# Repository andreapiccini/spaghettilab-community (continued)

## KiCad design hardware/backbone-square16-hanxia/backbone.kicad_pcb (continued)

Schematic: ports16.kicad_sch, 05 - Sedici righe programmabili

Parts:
C238, C239, C241, C242: 100nF; C_0603_1608Metric
J18, J19, J21, J22, J23, J24, J30, J31: HX PM2.54-1x8P TP-YQ; Hanxia_C42380985_1x08_Compact_Study; MPN HX PM2.54-1x8P TP-YQ; LCSC Part C42380985
Q30, Q31, Q32, Q33, Q34, Q35, Q36, Q37, Q44, Q45, Q46, Q47, Q48, Q49, Q50, Q51: AO3401A; SOT-23; MPN AO3401A; LCSC Part C15127
Q100, Q101, Q102, Q103, Q104, Q105, Q106, Q107, Q108, Q109, Q110, Q111, Q112, Q113, Q114, Q115: AO3400A; SOT-23; MPN AO3400A; LCSC Part C20917
RN1, RN2, RN3, RN4, RN5, RN6, RN7, RN8, RN9, RN10, RN11, RN12: 100k; YC164_4x0603_100k
U1: ESP32-S3-WROOM-1-N8R2; ESP32-S3-WROOM-1_FlexyPin_N8R2_TwoSideCourtyard; MPN ESP32-S3-WROOM-1-N8R2
U50, U51, U53, U54: 74CBTLV3125PW,118; TSSOP-14_L5.0-W4.4-P0.65-LS6.4-BL; MPN 74CBTLV3125PW,118; LCSC Part C456149

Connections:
3V3: C238.1, C239.1, C241.1, C242.1, RN9.1, RN9.2, RN9.3, RN9.4, RN10.1, RN10.2, RN10.3, RN10.4, RN11.1, RN11.2, RN11.3, RN11.4, RN12.1, RN12.2, RN12.3, RN12.4, U50.14 (VCC), U51.14 (VCC), U53.14 (VCC), U54.14 (VCC); also elsewhere on the board
3V3_ROWS: Q30.2 (S), Q31.2 (S), Q32.2 (S), Q33.2 (S), Q34.2 (S), Q35.2 (S), Q36.2 (S), Q37.2 (S), Q44.2 (S), Q45.2 (S), Q46.2 (S), Q47.2 (S), Q48.2 (S), Q49.2 (S), Q50.2 (S), Q51.2 (S), RN1.1, RN1.2, RN1.3, RN1.4, RN2.1, RN2.2, RN2.3, RN2.4, RN3.1, RN3.2, RN3.3, RN3.4, RN4.1, RN4.2, RN4.3, RN4.4; also elsewhere on the board
GND: C238.2, C239.2, C241.2, C242.2, Q100.2 (S), Q101.2 (S), Q102.2 (S), Q103.2 (S), Q104.2 (S), Q105.2 (S), Q106.2 (S), Q107.2 (S), Q108.2 (S), Q109.2 (S), Q110.2 (S), Q111.2 (S), Q112.2 (S), Q113.2 (S), Q114.2 (S), Q115.2 (S), RN5.5, RN5.6, RN5.7, RN5.8, RN6.5, RN6.6, RN6.7, RN6.8, RN7.5, RN7.6, RN7.7, RN7.8, RN8.5, RN8.6, RN8.7, RN8.8, U50.7 (GND), U51.7 (GND), U53.7 (GND), U54.7 (GND); also elsewhere on the board
GPIO1: U1.39 (IO1), U50.2 (A); also elsewhere on the board
GPIO2: U1.38 (IO2), U53.2 (A); also elsewhere on the board
GPIO3: U1.15 (IO3), U50.5 (A); also elsewhere on the board
GPIO4: U1.4 (IO4), U51.2 (A); also elsewhere on the board
GPIO6: U1.6 (IO6), U50.9 (A); also elsewhere on the board
GPIO7: U1.7 (IO7), U50.12 (A); also elsewhere on the board
GPIO8: U1.12 (IO8), U53.5 (A); also elsewhere on the board
GPIO9: U1.17 (IO9), U53.9 (A); also elsewhere on the board
GPIO10: U1.18 (IO10), U53.12 (A); also elsewhere on the board
GPIO35: U1.28 (IO35), U51.5 (A); also elsewhere on the board
GPIO36: U1.29 (IO36), U51.9 (A); also elsewhere on the board
GPIO37: U1.30 (IO37), U51.12 (A); also elsewhere on the board
GPIO38: U1.31 (IO38), U54.2 (A); also elsewhere on the board
GPIO39: U1.32 (IO39), U54.5 (A); also elsewhere on the board
GPIO40: U1.33 (IO40), U54.9 (A); also elsewhere on the board
GPIO41: U1.34 (IO41), U54.12 (A); also elsewhere on the board
ROW_L01: J18.1, J19.1, J21.1, J30.1, Q30.3 (D), Q100.3 (D), U50.3 (B); also elsewhere on the board
ROW_L01_ISO_N: RN9.5, U50.1 (OE_N); also elsewhere on the board
ROW_L01_NG: Q100.1 (G), RN5.1; also elsewhere on the board
ROW_L01_PG: Q30.1 (G), RN1.5; also elsewhere on the board
ROW_L02: J18.2, J19.2, J21.2, J30.2, Q31.3 (D), Q101.3 (D), U50.6 (B); also elsewhere on the board
ROW_L02_ISO_N: RN9.6, U50.4 (OE_N); also elsewhere on the board
ROW_L02_NG: Q101.1 (G), RN5.2; also elsewhere on the board
ROW_L02_PG: Q31.1 (G), RN1.6; also elsewhere on the board
ROW_L03: J18.3, J19.3, J21.3, J30.3, Q32.3 (D), Q102.3 (D), U50.8 (B); also elsewhere on the board
ROW_L03_ISO_N: RN9.7, U50.10 (OE_N); also elsewhere on the board
ROW_L03_NG: Q102.1 (G), RN5.3; also elsewhere on the board
ROW_L03_PG: Q32.1 (G), RN1.7; also elsewhere on the board
ROW_L04: J18.4, J19.4, J21.4, J30.4, Q33.3 (D), Q103.3 (D), U50.11 (B); also elsewhere on the board
ROW_L04_ISO_N: RN9.8, U50.13 (OE_N); also elsewhere on the board
ROW_L04_NG: Q103.1 (G), RN5.4; also elsewhere on the board
ROW_L04_PG: Q33.1 (G), RN1.8; also elsewhere on the board
ROW_L05: J18.5, J19.5, J21.5, J30.5, Q34.3 (D), Q104.3 (D), U51.3 (B); also elsewhere on the board
ROW_L05_ISO_N: RN10.5, U51.1 (OE_N); also elsewhere on the board
ROW_L05_NG: Q104.1 (G), RN6.1; also elsewhere on the board
ROW_L05_PG: Q34.1 (G), RN2.5; also elsewhere on the board
ROW_L06: J18.6, J19.6, J21.6, J30.6, Q35.3 (D), Q105.3 (D), U51.6 (B); also elsewhere on the board
ROW_L06_ISO_N: RN10.6, U51.4 (OE_N); also elsewhere on the board
ROW_L06_NG: Q105.1 (G), RN6.2; also elsewhere on the board
ROW_L06_PG: Q35.1 (G), RN2.6; also elsewhere on the board
ROW_L07: J18.7, J19.7, J21.7, J30.7, Q36.3 (D), Q106.3 (D), U51.8 (B); also elsewhere on the board
ROW_L07_ISO_N: RN10.7, U51.10 (OE_N); also elsewhere on the board
ROW_L07_NG: Q106.1 (G), RN6.3; also elsewhere on the board
ROW_L07_PG: Q36.1 (G), RN2.7; also elsewhere on the board
ROW_L08: J18.8, J19.8, J21.8, J30.8, Q37.3 (D), Q107.3 (D), U51.11 (B); also elsewhere on the board
ROW_L08_ISO_N: RN10.8, U51.13 (OE_N); also elsewhere on the board
ROW_L08_NG: Q107.1 (G), RN6.4; also elsewhere on the board
ROW_L08_PG: Q37.1 (G), RN2.8; also elsewhere on the board
ROW_R01: J22.1, J23.1, J24.1, J31.1, Q44.3 (D), Q108.3 (D), U53.3 (B); also elsewhere on the board
ROW_R01_ISO_N: RN11.5, U53.1 (OE_N); also elsewhere on the board
ROW_R01_NG: Q108.1 (G), RN7.1; also elsewhere on the board
ROW_R01_PG: Q44.1 (G), RN3.5; also elsewhere on the board
ROW_R02: J22.2, J23.2, J24.2, J31.2, Q45.3 (D), Q109.3 (D), U53.6 (B); also elsewhere on the board
ROW_R02_ISO_N: RN11.6, U53.4 (OE_N); also elsewhere on the board
ROW_R02_NG: Q109.1 (G), RN7.2; also elsewhere on the board
ROW_R02_PG: Q45.1 (G), RN3.6; also elsewhere on the board
ROW_R03: J22.3, J23.3, J24.3, J31.3, Q46.3 (D), Q110.3 (D), U53.8 (B); also elsewhere on the board
ROW_R03_ISO_N: RN11.7, U53.10 (OE_N); also elsewhere on the board
ROW_R03_NG: Q110.1 (G), RN7.3; also elsewhere on the board
ROW_R03_PG: Q46.1 (G), RN3.7; also elsewhere on the board
ROW_R04: J22.4, J23.4, J24.4, J31.4, Q47.3 (D), Q111.3 (D), U53.11 (B); also elsewhere on the board
ROW_R04_ISO_N: RN11.8, U53.13 (OE_N); also elsewhere on the board
ROW_R04_NG: Q111.1 (G), RN7.4; also elsewhere on the board
ROW_R04_PG: Q47.1 (G), RN3.8; also elsewhere on the board
ROW_R05: J22.5, J23.5, J24.5, J31.5, Q48.3 (D), Q112.3 (D), U54.3 (B); also elsewhere on the board
ROW_R05_ISO_N: RN12.5, U54.1 (OE_N); also elsewhere on the board
ROW_R05_NG: Q112.1 (G), RN8.1; also elsewhere on the board
ROW_R05_PG: Q48.1 (G), RN4.5; also elsewhere on the board
ROW_R06: J22.6, J23.6, J24.6, J31.6, Q49.3 (D), Q113.3 (D), U54.6 (B); also elsewhere on the board
ROW_R06_ISO_N: RN12.6, U54.4 (OE_N); also elsewhere on the board
ROW_R06_NG: Q113.1 (G), RN8.2; also elsewhere on the board
ROW_R06_PG: Q49.1 (G), RN4.6; also elsewhere on the board
ROW_R07: J22.7, J23.7, J24.7, J31.7, Q50.3 (D), Q114.3 (D), U54.8 (B); also elsewhere on the board
ROW_R07_ISO_N: RN12.7, U54.10 (OE_N); also elsewhere on the board
ROW_R07_NG: Q114.1 (G), RN8.3; also elsewhere on the board
ROW_R07_PG: Q50.1 (G), RN4.7; also elsewhere on the board
ROW_R08: J22.8, J23.8, J24.8, J31.8, Q51.3 (D), Q115.3 (D), U54.11 (B); also elsewhere on the board
ROW_R08_ISO_N: RN12.8, U54.13 (OE_N); also elsewhere on the board
ROW_R08_NG: Q115.1 (G), RN8.4; also elsewhere on the board
ROW_R08_PG: Q51.1 (G), RN4.8; also elsewhere on the board

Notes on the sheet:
16 RIGHE PROGRAMMABILI | VCC3V3 / GND / GPIO / HI-Z
A1 | pad 39 | ROW_L01
PG=0:VCC | NG=1:GND | ISO_N=0:GPIO
A2 | pad 15 | ROW_L02
A3 | pad 6 | ROW_L03
A4 | pad 7 | ROW_L04
A5 | pad 4 | ROW_L05
A6 | pad 28 | ROW_L06
A7 | pad 29 | ROW_L07
A8 | pad 30 | ROW_L08
B1 | pad 38 | ROW_R01
B2 | pad 12 | ROW_R02
B3 | pad 17 | ROW_R03
B4 | pad 18 | ROW_R04
B5 | pad 31 | ROW_R05
B6 | pad 32 | ROW_R06
B7 | pad 33 | ROW_R07
B8 | pad 34 | ROW_R08
ALIMENTAZIONE DEI4ISOLATORI
Ogni integrato ha4canali. UnitaE=alimentazione; bypass100nF.
ADC S3 / ADC S31
ADC S3 / DIG S31
DIG S3 / ADC S31
ADC DISTRIBUITI: A = 5 S3 / 4 S31; B = 4 S3 / 5 S31. Totale 9 / 9. U1A = servizi sul foglio principale; U1B..Q = contatti reali dello stesso socket. J18..J31: le unita A..H sono gli 8 contatti dello stesso connettore fisico. Percorso continuo per ogni riga: U1 -> isolatore -> 4 contatti Hanxia. Le 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

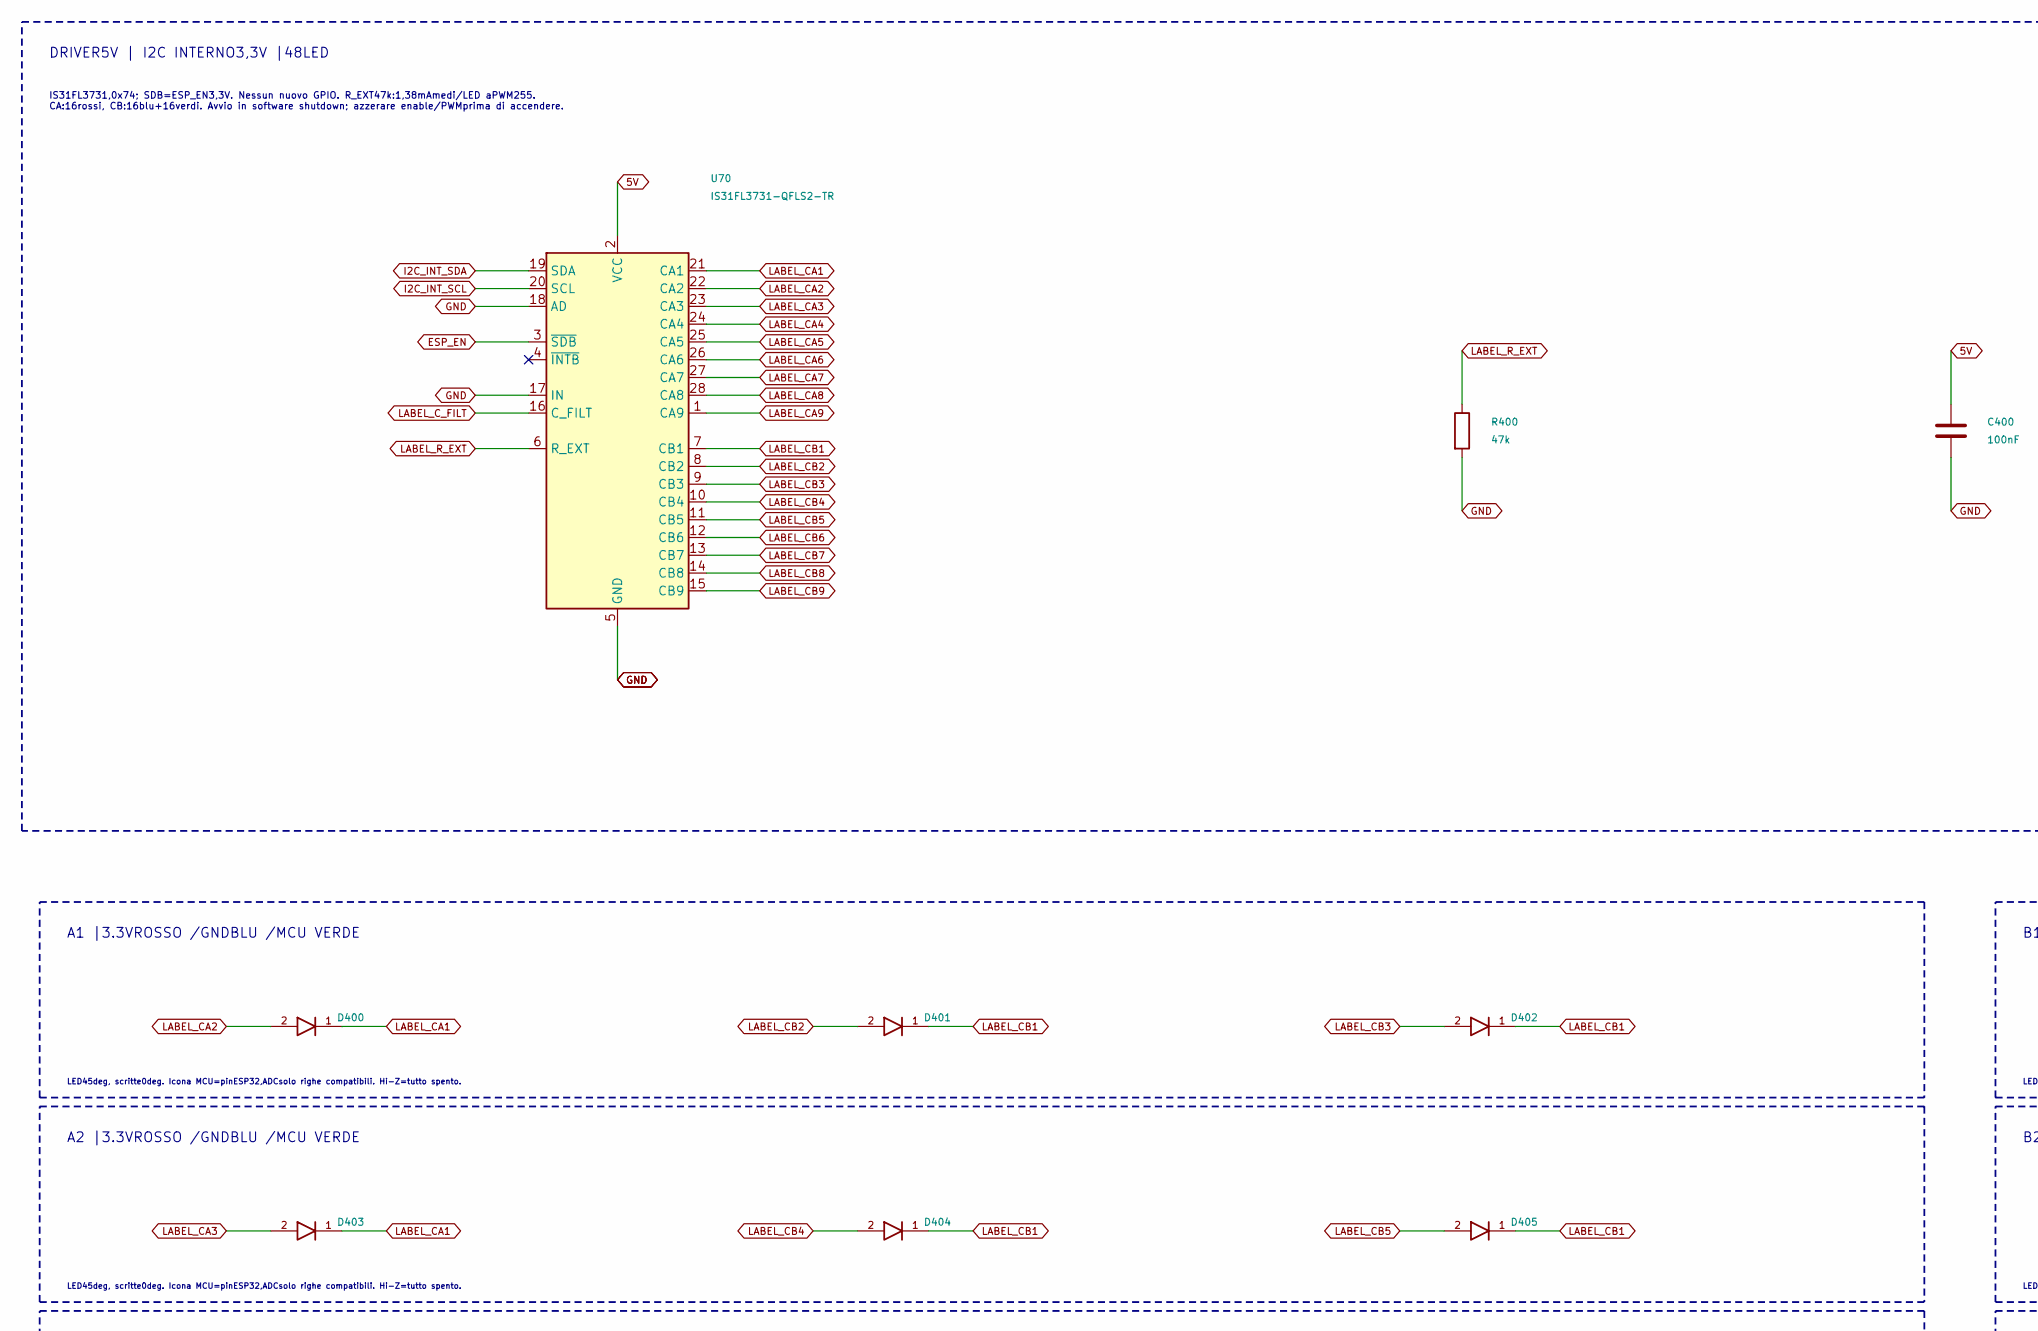
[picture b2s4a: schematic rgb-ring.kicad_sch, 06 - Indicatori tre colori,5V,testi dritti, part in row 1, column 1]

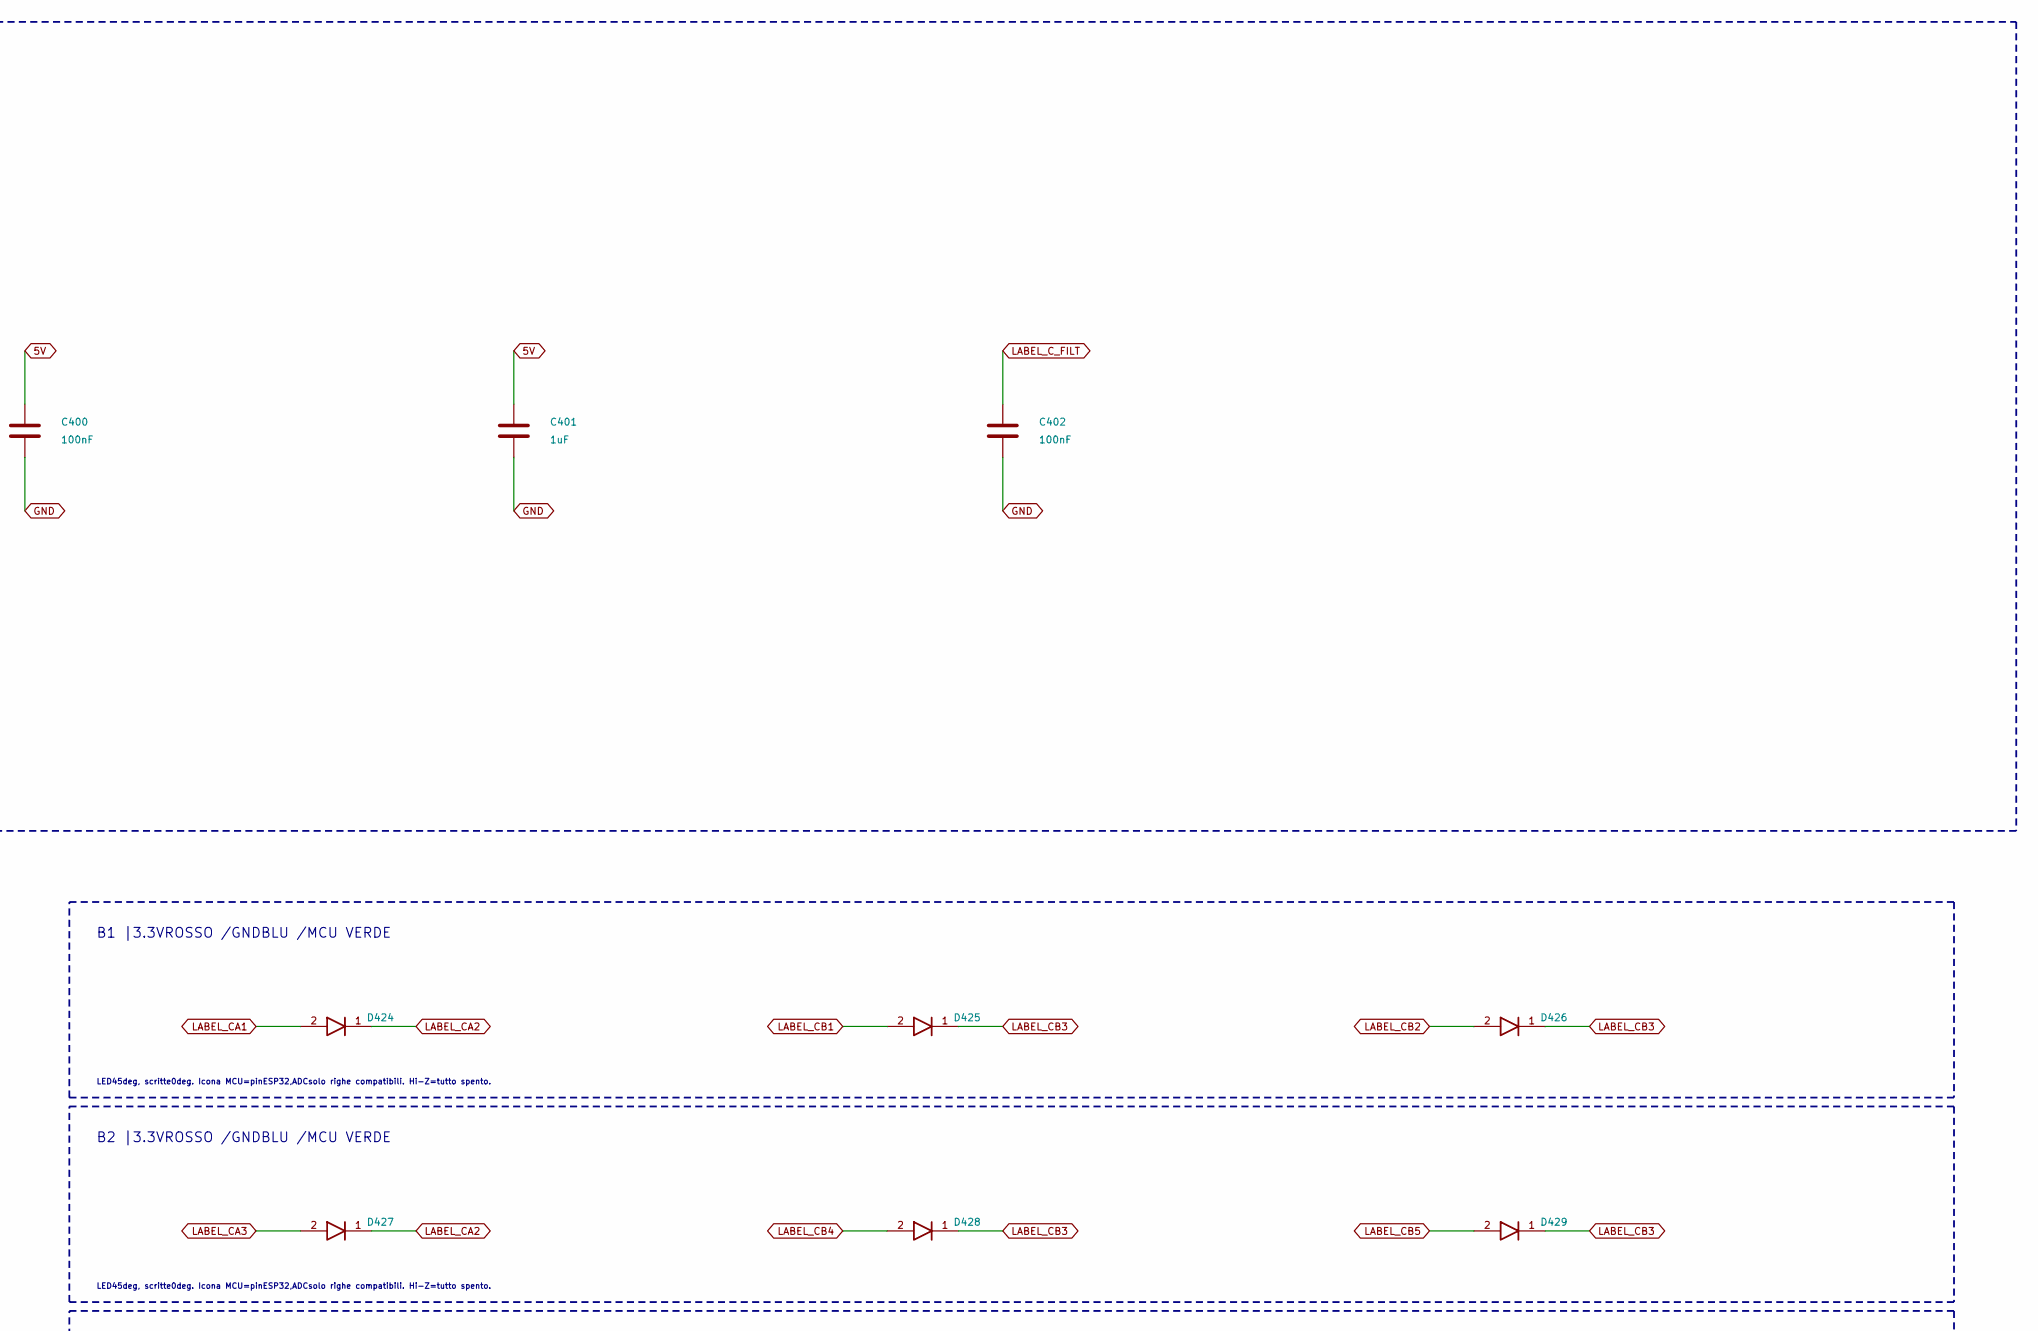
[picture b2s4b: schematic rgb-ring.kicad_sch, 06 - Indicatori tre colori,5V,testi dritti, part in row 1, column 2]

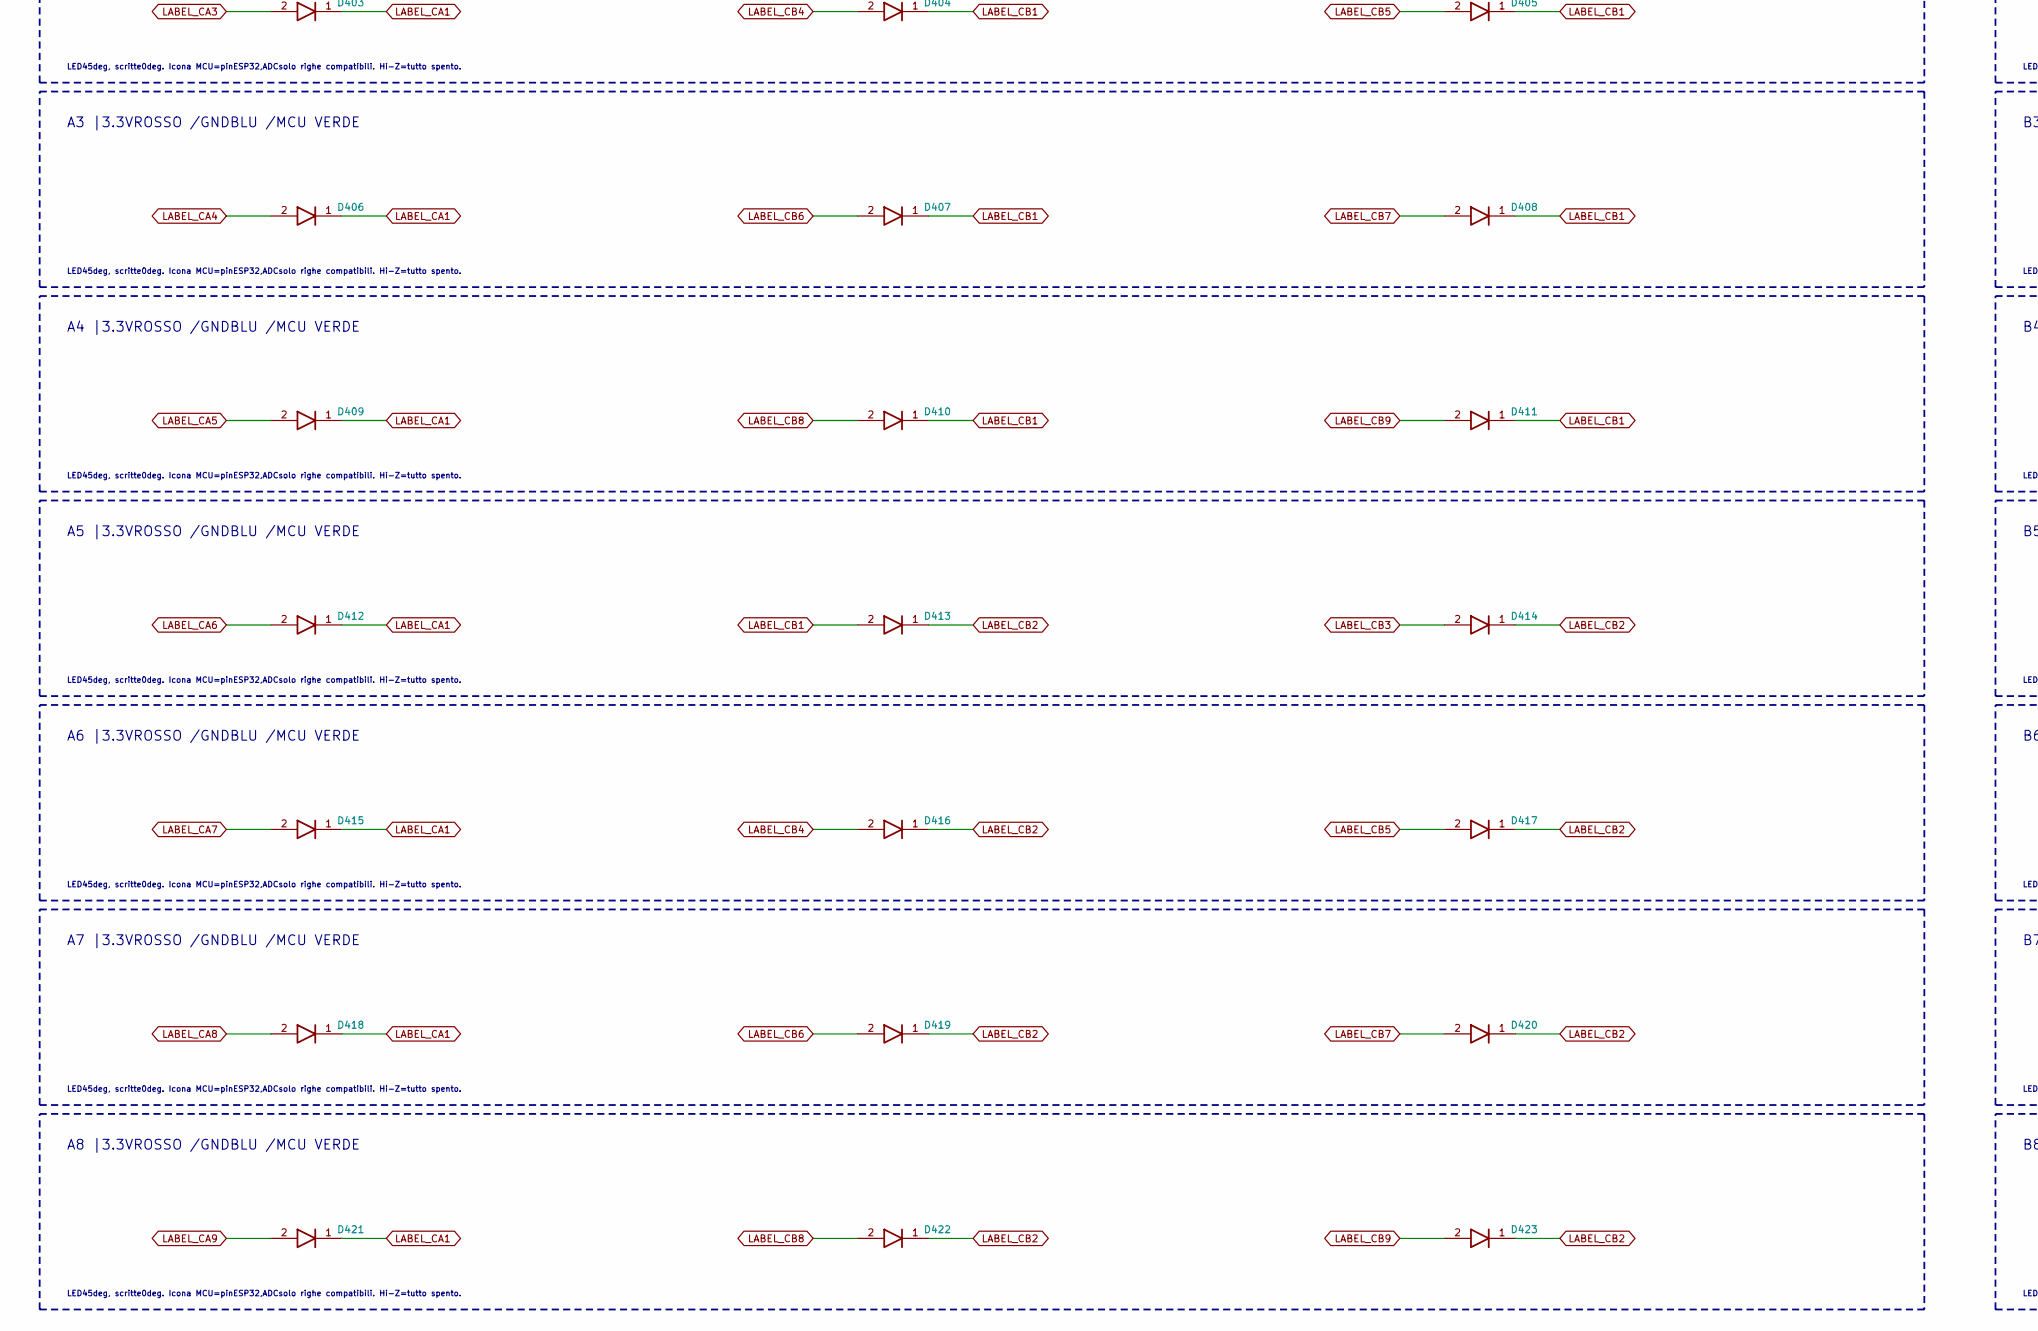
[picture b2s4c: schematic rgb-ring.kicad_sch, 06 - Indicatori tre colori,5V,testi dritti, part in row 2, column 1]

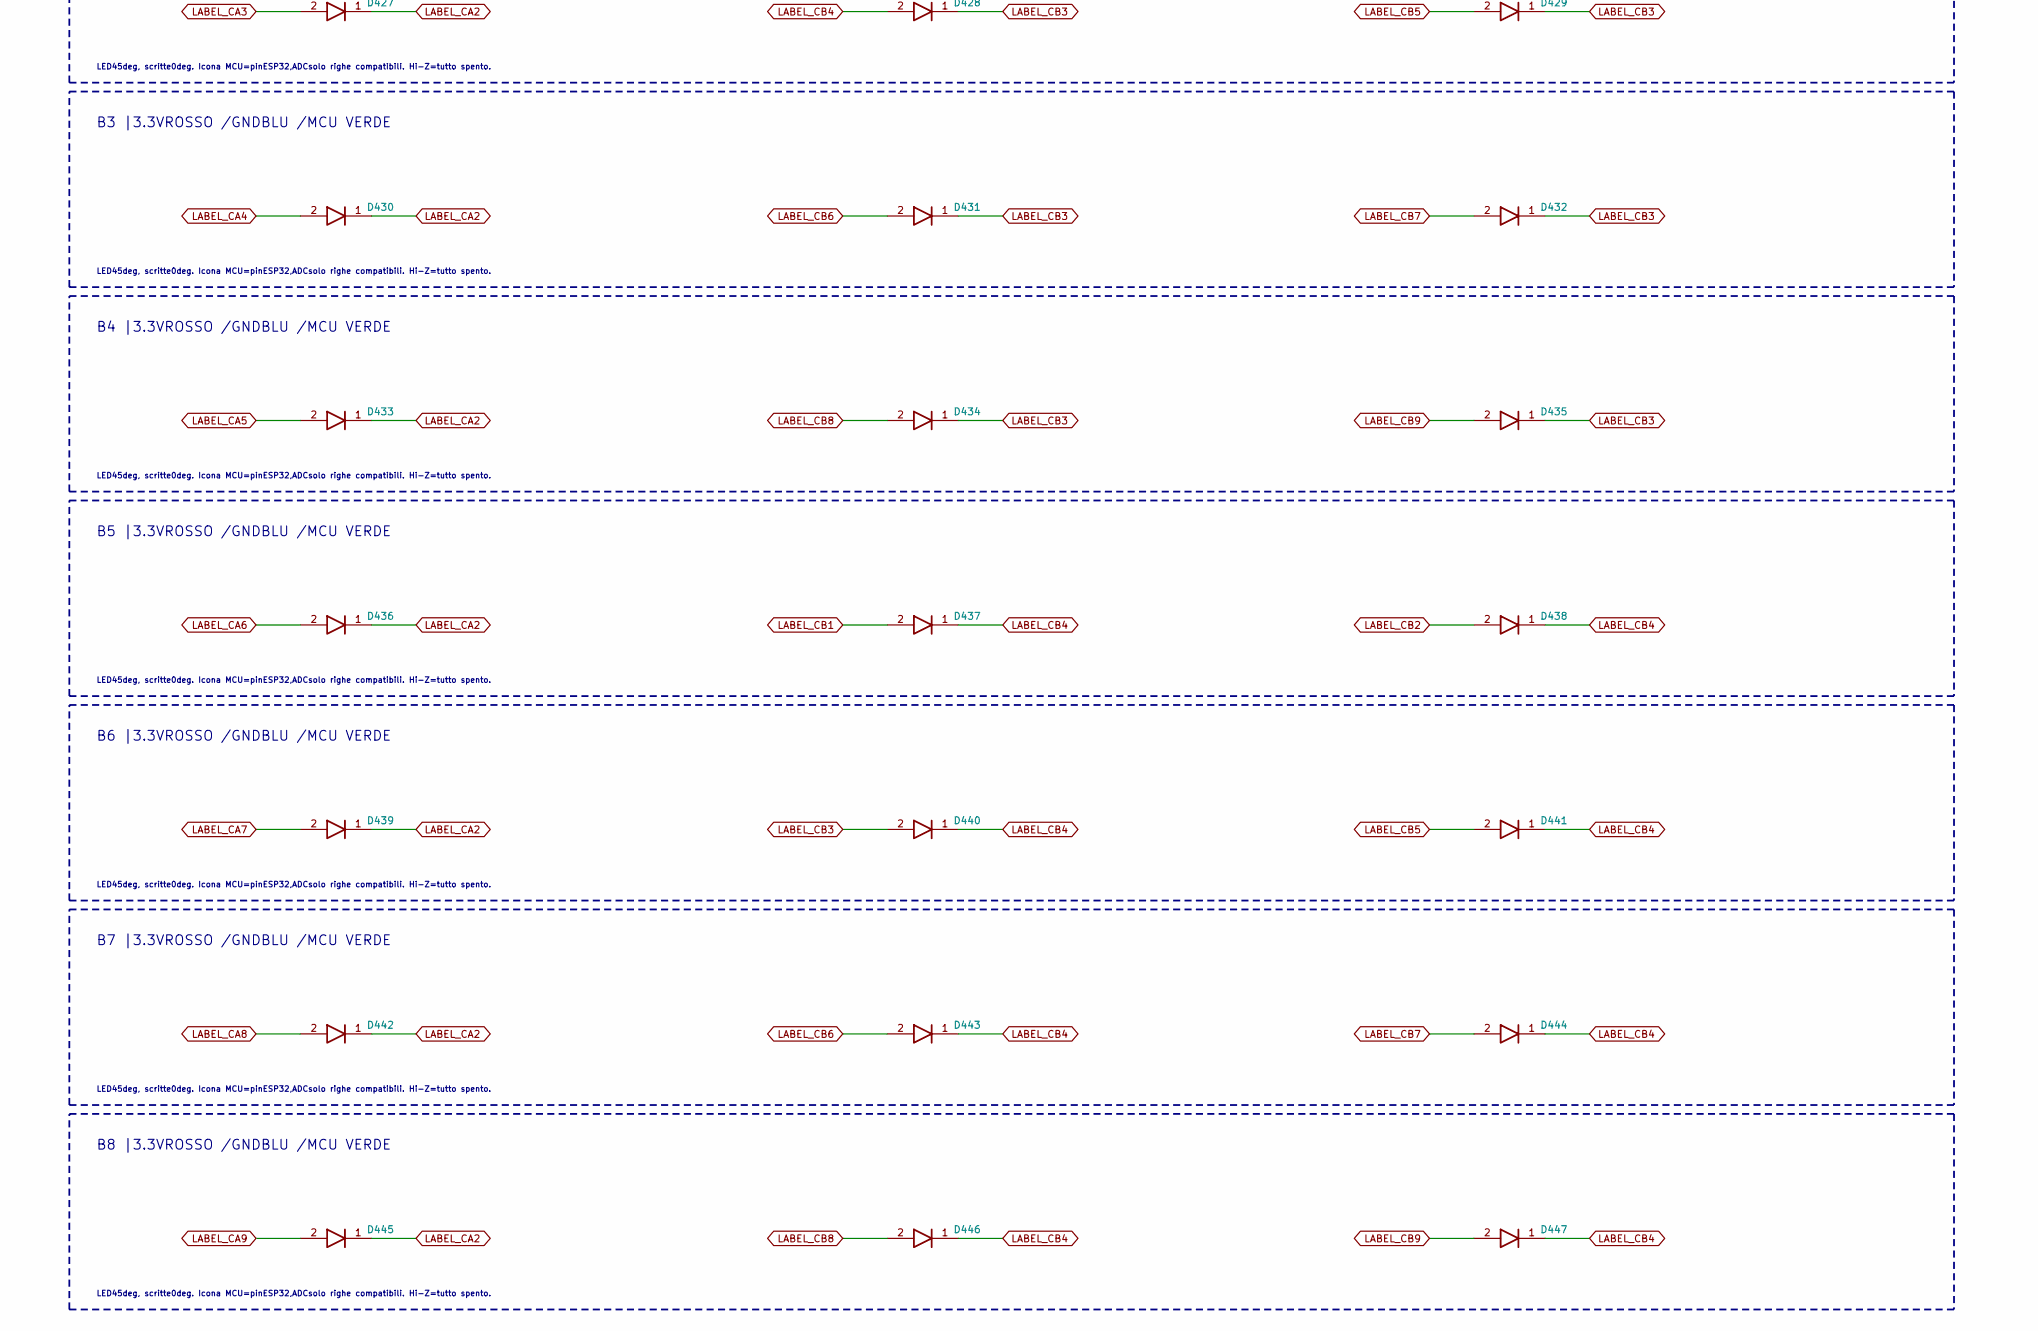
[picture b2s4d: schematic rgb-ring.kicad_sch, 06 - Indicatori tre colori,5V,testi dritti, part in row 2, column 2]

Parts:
C400, C402: 100nF; C_0603_1608Metric; MPN CL10B104KB8NNNC; LCSC Part C1591
C401: 1uF; C_0603_1608Metric; MPN CL10A105KB8NNNC; LCSC Part C15849
D400, D403, D406, D409, D412, D415, D418, D421, D424, D427, D430, D433, D436, D439, D442, D445: XL-3216SURC-FB; XINGLIGHT_XL3216_Reverse_Word_Window; MPN XL-3216SURC-FB; LCSC Part C3646938
D401, D404, D407, D410, D413, D416, D419, D422, D425, D428, D431, D434, D437, D440, D443, D446: XL-3216UBC-FB; XINGLIGHT_XL3216_Reverse_Word_Window; MPN XL-3216UBC-FB; LCSC Part C3646941
D402, D405, D408, D411, D414, D417, D420, D423, D426, D429, D432, D435, D438, D441, D444, D447: XL-3216UGC-FB; XINGLIGHT_XL3216_Reverse_Word_Window; MPN XL-3216UGC-FB; LCSC Part C3646937
R400: 47k; R_0603_1608Metric; MPN 0603WAF4702T5E; LCSC Part C25819
U70: IS31FL3731-QFLS2-TR; IS31FL3731_QFN28_4x4; MPN IS31FL3731-QFLS2-TR; LCSC Part C191206

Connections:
5V: C400.1, C401.1, U70.2 (VCC); also elsewhere on the board
ESP_EN: U70.3 (~SDB); also elsewhere on the board
GND: C400.2, C401.2, C402.2, R400.2, U70.5 (GND), U70.17 (IN), U70.18 (AD), U70.29 (GND); also elsewhere on the board
I2C_INT_SCL: U70.20 (SCL); also elsewhere on the board
I2C_INT_SDA: U70.19 (SDA); also elsewhere on the board
LABEL_CA1: D400.1 (K), D403.1 (K), D406.1 (K), D409.1 (K), D412.1 (K), D415.1 (K), D418.1 (K), D421.1 (K), D424.2 (A), U70.21 (CA1); also elsewhere on the board
LABEL_CA2: D400.2 (A), D424.1 (K), D427.1 (K), D430.1 (K), D433.1 (K), D436.1 (K), D439.1 (K), D442.1 (K), D445.1 (K), U70.22 (CA2); also elsewhere on the board
LABEL_CA3: D403.2 (A), D427.2 (A), U70.23 (CA3); also elsewhere on the board
LABEL_CA4: D406.2 (A), D430.2 (A), U70.24 (CA4); also elsewhere on the board
LABEL_CA5: D409.2 (A), D433.2 (A), U70.25 (CA5); also elsewhere on the board
LABEL_CA6: D412.2 (A), D436.2 (A), U70.26 (CA6); also elsewhere on the board
LABEL_CA7: D415.2 (A), D439.2 (A), U70.27 (CA7); also elsewhere on the board
LABEL_CA8: D418.2 (A), D442.2 (A), U70.28 (CA8); also elsewhere on the board
LABEL_CA9: D421.2 (A), D445.2 (A), U70.1 (CA9); also elsewhere on the board
LABEL_CB1: D401.1 (K), D402.1 (K), D404.1 (K), D405.1 (K), D407.1 (K), D408.1 (K), D410.1 (K), D411.1 (K), D413.2 (A), D425.2 (A), D437.2 (A), U70.7 (CB1); also elsewhere on the board
LABEL_CB2: D401.2 (A), D413.1 (K), D414.1 (K), D416.1 (K), D417.1 (K), D419.1 (K), D420.1 (K), D422.1 (K), D423.1 (K), D426.2 (A), D438.2 (A), U70.8 (CB2); also elsewhere on the board
LABEL_CB3: D402.2 (A), D414.2 (A), D425.1 (K), D426.1 (K), D428.1 (K), D429.1 (K), D431.1 (K), D432.1 (K), D434.1 (K), D435.1 (K), D440.2 (A), U70.9 (CB3); also elsewhere on the board
LABEL_CB4: D404.2 (A), D416.2 (A), D428.2 (A), D437.1 (K), D438.1 (K), D440.1 (K), D441.1 (K), D443.1 (K), D444.1 (K), D446.1 (K), D447.1 (K), U70.10 (CB4); also elsewhere on the board
LABEL_CB5: D405.2 (A), D417.2 (A), D429.2 (A), D441.2 (A), U70.11 (CB5); also elsewhere on the board
LABEL_CB6: D407.2 (A), D419.2 (A), D431.2 (A), D443.2 (A), U70.12 (CB6); also elsewhere on the board
LABEL_CB7: D408.2 (A), D420.2 (A), D432.2 (A), D444.2 (A), U70.13 (CB7); also elsewhere on the board
LABEL_CB8: D410.2 (A), D422.2 (A), D434.2 (A), D446.2 (A), U70.14 (CB8); also elsewhere on the board
LABEL_CB9: D411.2 (A), D423.2 (A), D435.2 (A), D447.2 (A), U70.15 (CB9); also elsewhere on the board
LABEL_C_FILT: C402.1, U70.16 (C_FILT)
LABEL_R_EXT: R400.1, U70.6 (R_EXT)

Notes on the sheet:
DRIVER5V | I2C INTERNO3,3V |48LED
IS31FL3731,0x74; SDB=ESP_EN3,3V. Nessun nuovo GPIO. R_EXT47k:1,38mAmedi/LED aPWM255. CA:16rossi, CB:16blu+16verdi. Avvio in software shutdown; azzerare enable/PWMprima di accendere.
A1 |3.3VROSSO /GNDBLU /MCU VERDE
LED45deg, scritte0deg. Icona MCU=pinESP32,ADCsolo righe compatibili. Hi-Z=tutto spento.
A2 |3.3VROSSO /GNDBLU /MCU VERDE
A3 |3.3VROSSO /GNDBLU /MCU VERDE
A4 |3.3VROSSO /GNDBLU /MCU VERDE
A5 |3.3VROSSO /GNDBLU /MCU VERDE
A6 |3.3VROSSO /GNDBLU /MCU VERDE
A7 |3.3VROSSO /GNDBLU /MCU VERDE
A8 |3.3VROSSO /GNDBLU /MCU VERDE
B1 |3.3VROSSO /GNDBLU /MCU VERDE
B2 |3.3VROSSO /GNDBLU /MCU VERDE
B3 |3.3VROSSO /GNDBLU /MCU VERDE
B4 |3.3VROSSO /GNDBLU /MCU VERDE
B5 |3.3VROSSO /GNDBLU /MCU VERDE
B6 |3.3VROSSO /GNDBLU /MCU VERDE
B7 |3.3VROSSO /GNDBLU /MCU VERDE
B8 |3.3VROSSO /GNDBLU /MCU VERDE
